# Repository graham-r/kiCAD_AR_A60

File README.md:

# A&R A60 Amplifier KICAD projects

NOTE: These are experiments in using KICAD - they are untested as they have not been built
(unless stated otherwise in the README file in a specific directory).

The projects contained in this repository are all based on the A&R A60 or A60AP integrated
amplifiers, currently limited to issue 8 (25502 onwards schematics).

The copyright of the circuits remain with the original owners, the Schematic and hardware
copyright are open source.

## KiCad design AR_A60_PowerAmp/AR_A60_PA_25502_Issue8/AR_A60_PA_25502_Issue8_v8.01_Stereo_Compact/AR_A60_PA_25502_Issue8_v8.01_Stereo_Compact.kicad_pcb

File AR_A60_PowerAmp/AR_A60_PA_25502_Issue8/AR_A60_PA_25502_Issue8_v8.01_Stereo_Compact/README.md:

# A&R A60 Amplifier KICAD projects

Version 8.01 differences

Compact style PCB Power & speaker fuses removed Common input socket (Left & Right) +/-36v Power rails decoupled between power amp stage & input stage

NOTE: These are experiments in using KICAD - they are untested as they have not been built (unless stated otherwise in the README file in a specific directory).

The projects contained in this repository are all based on the A&R A60 or A60AP integrated amplifiers, currently limited to issue 8 (25502 onwards schematics).

The copyright of the circuits remain with the original owners, the Schematic and hardware copyright are open source.

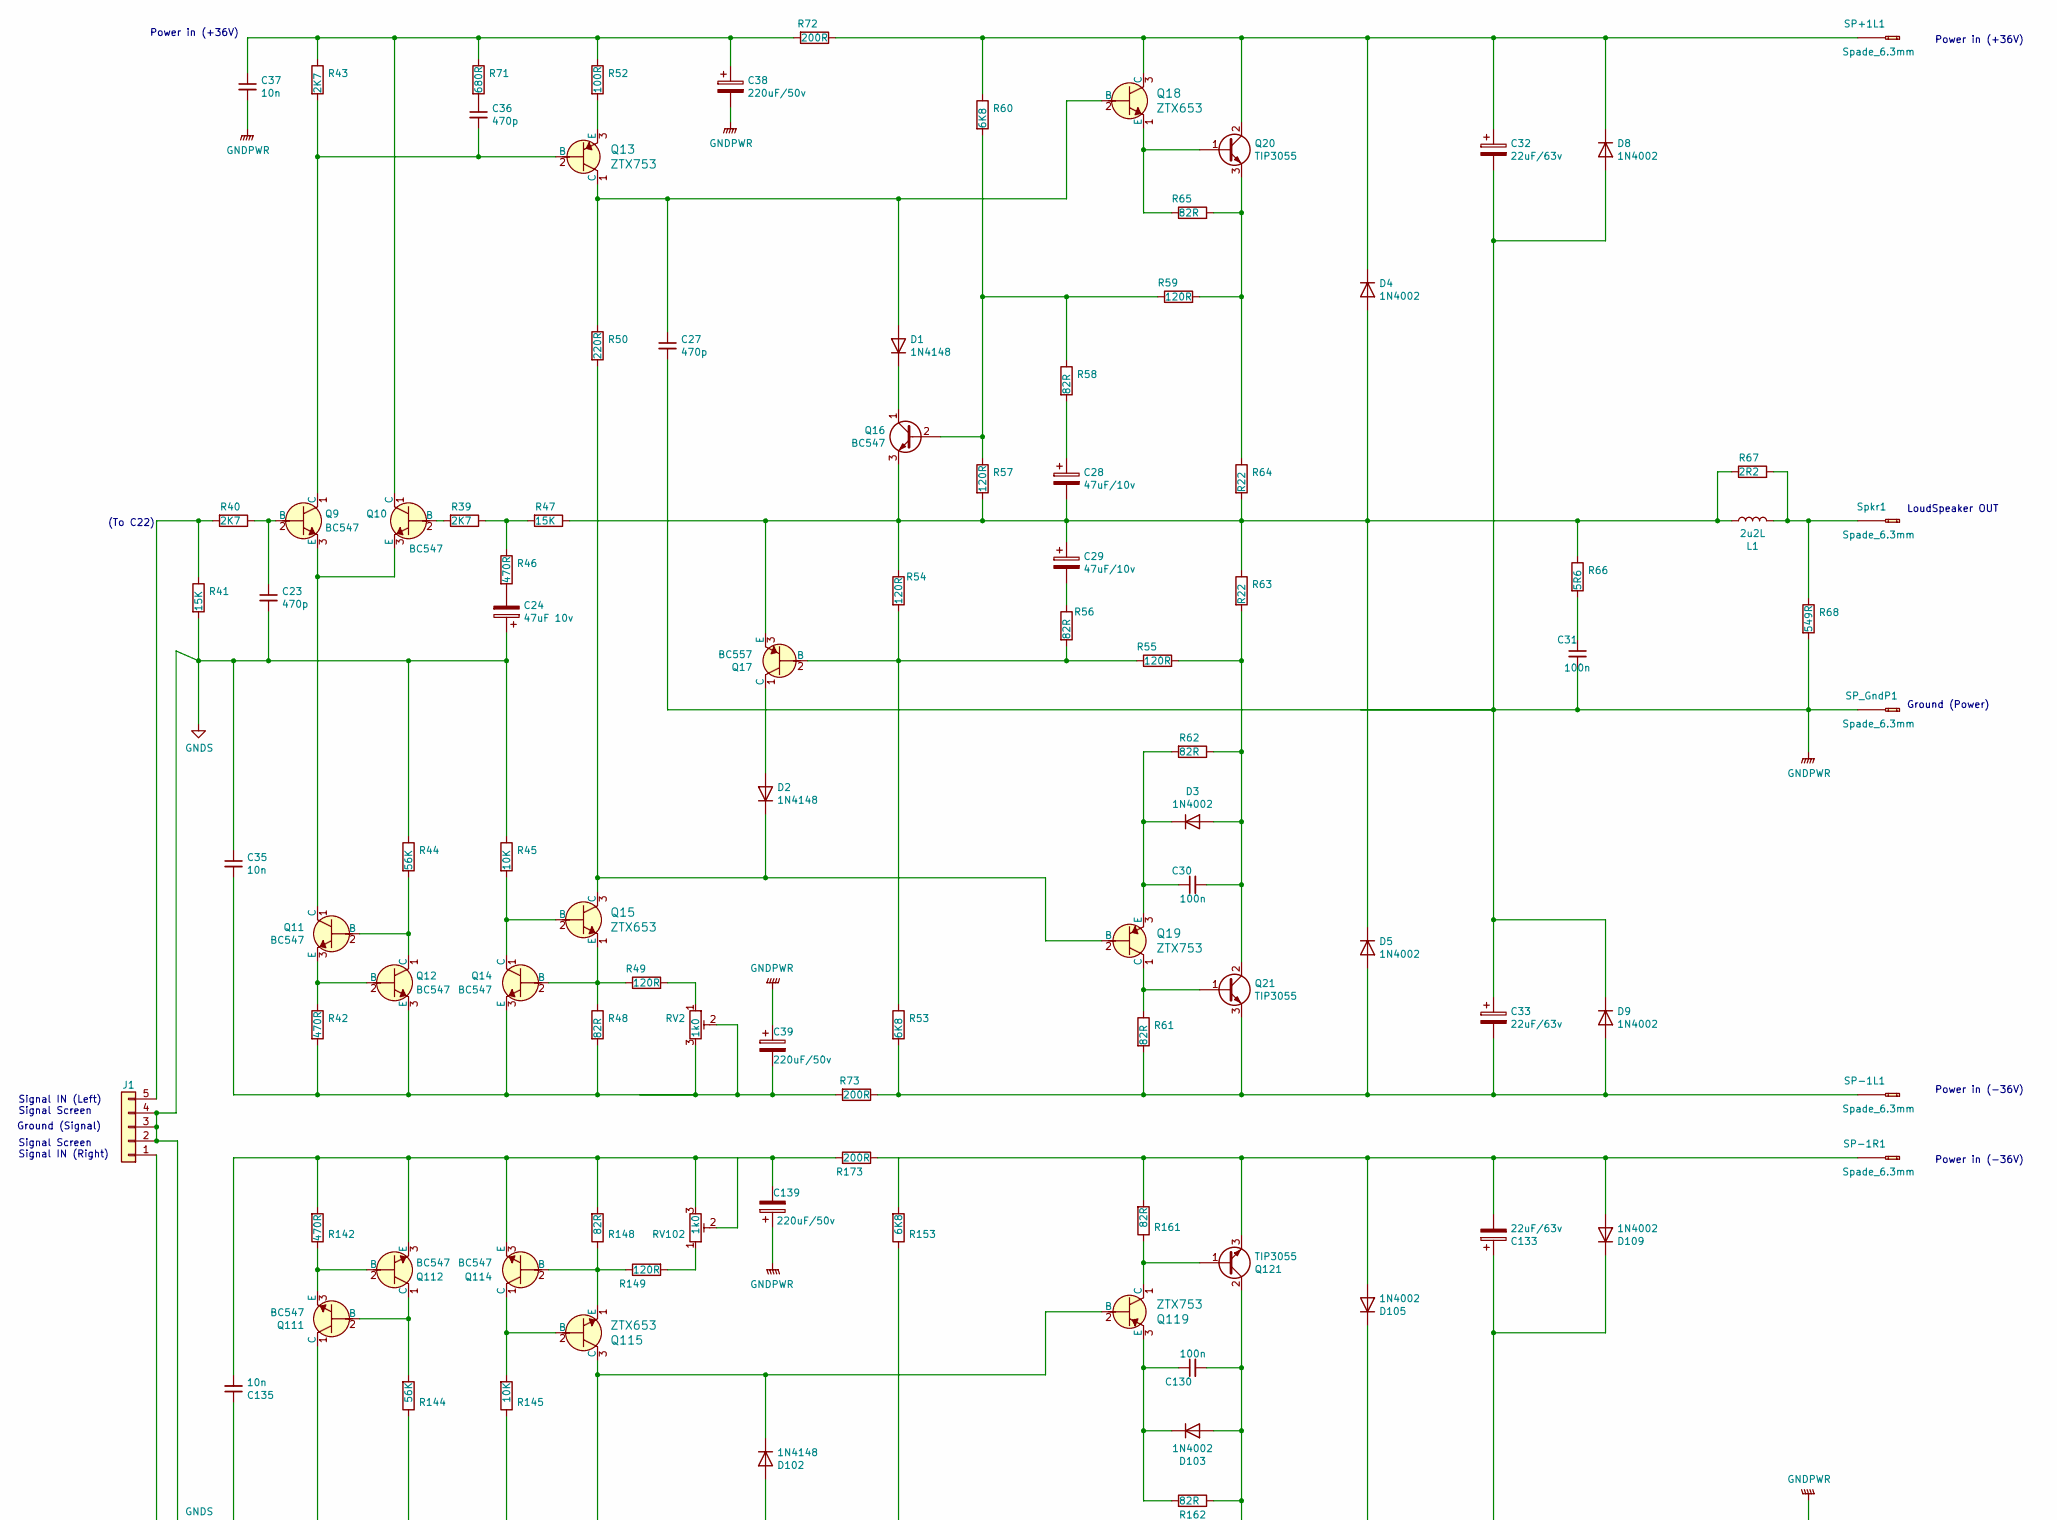
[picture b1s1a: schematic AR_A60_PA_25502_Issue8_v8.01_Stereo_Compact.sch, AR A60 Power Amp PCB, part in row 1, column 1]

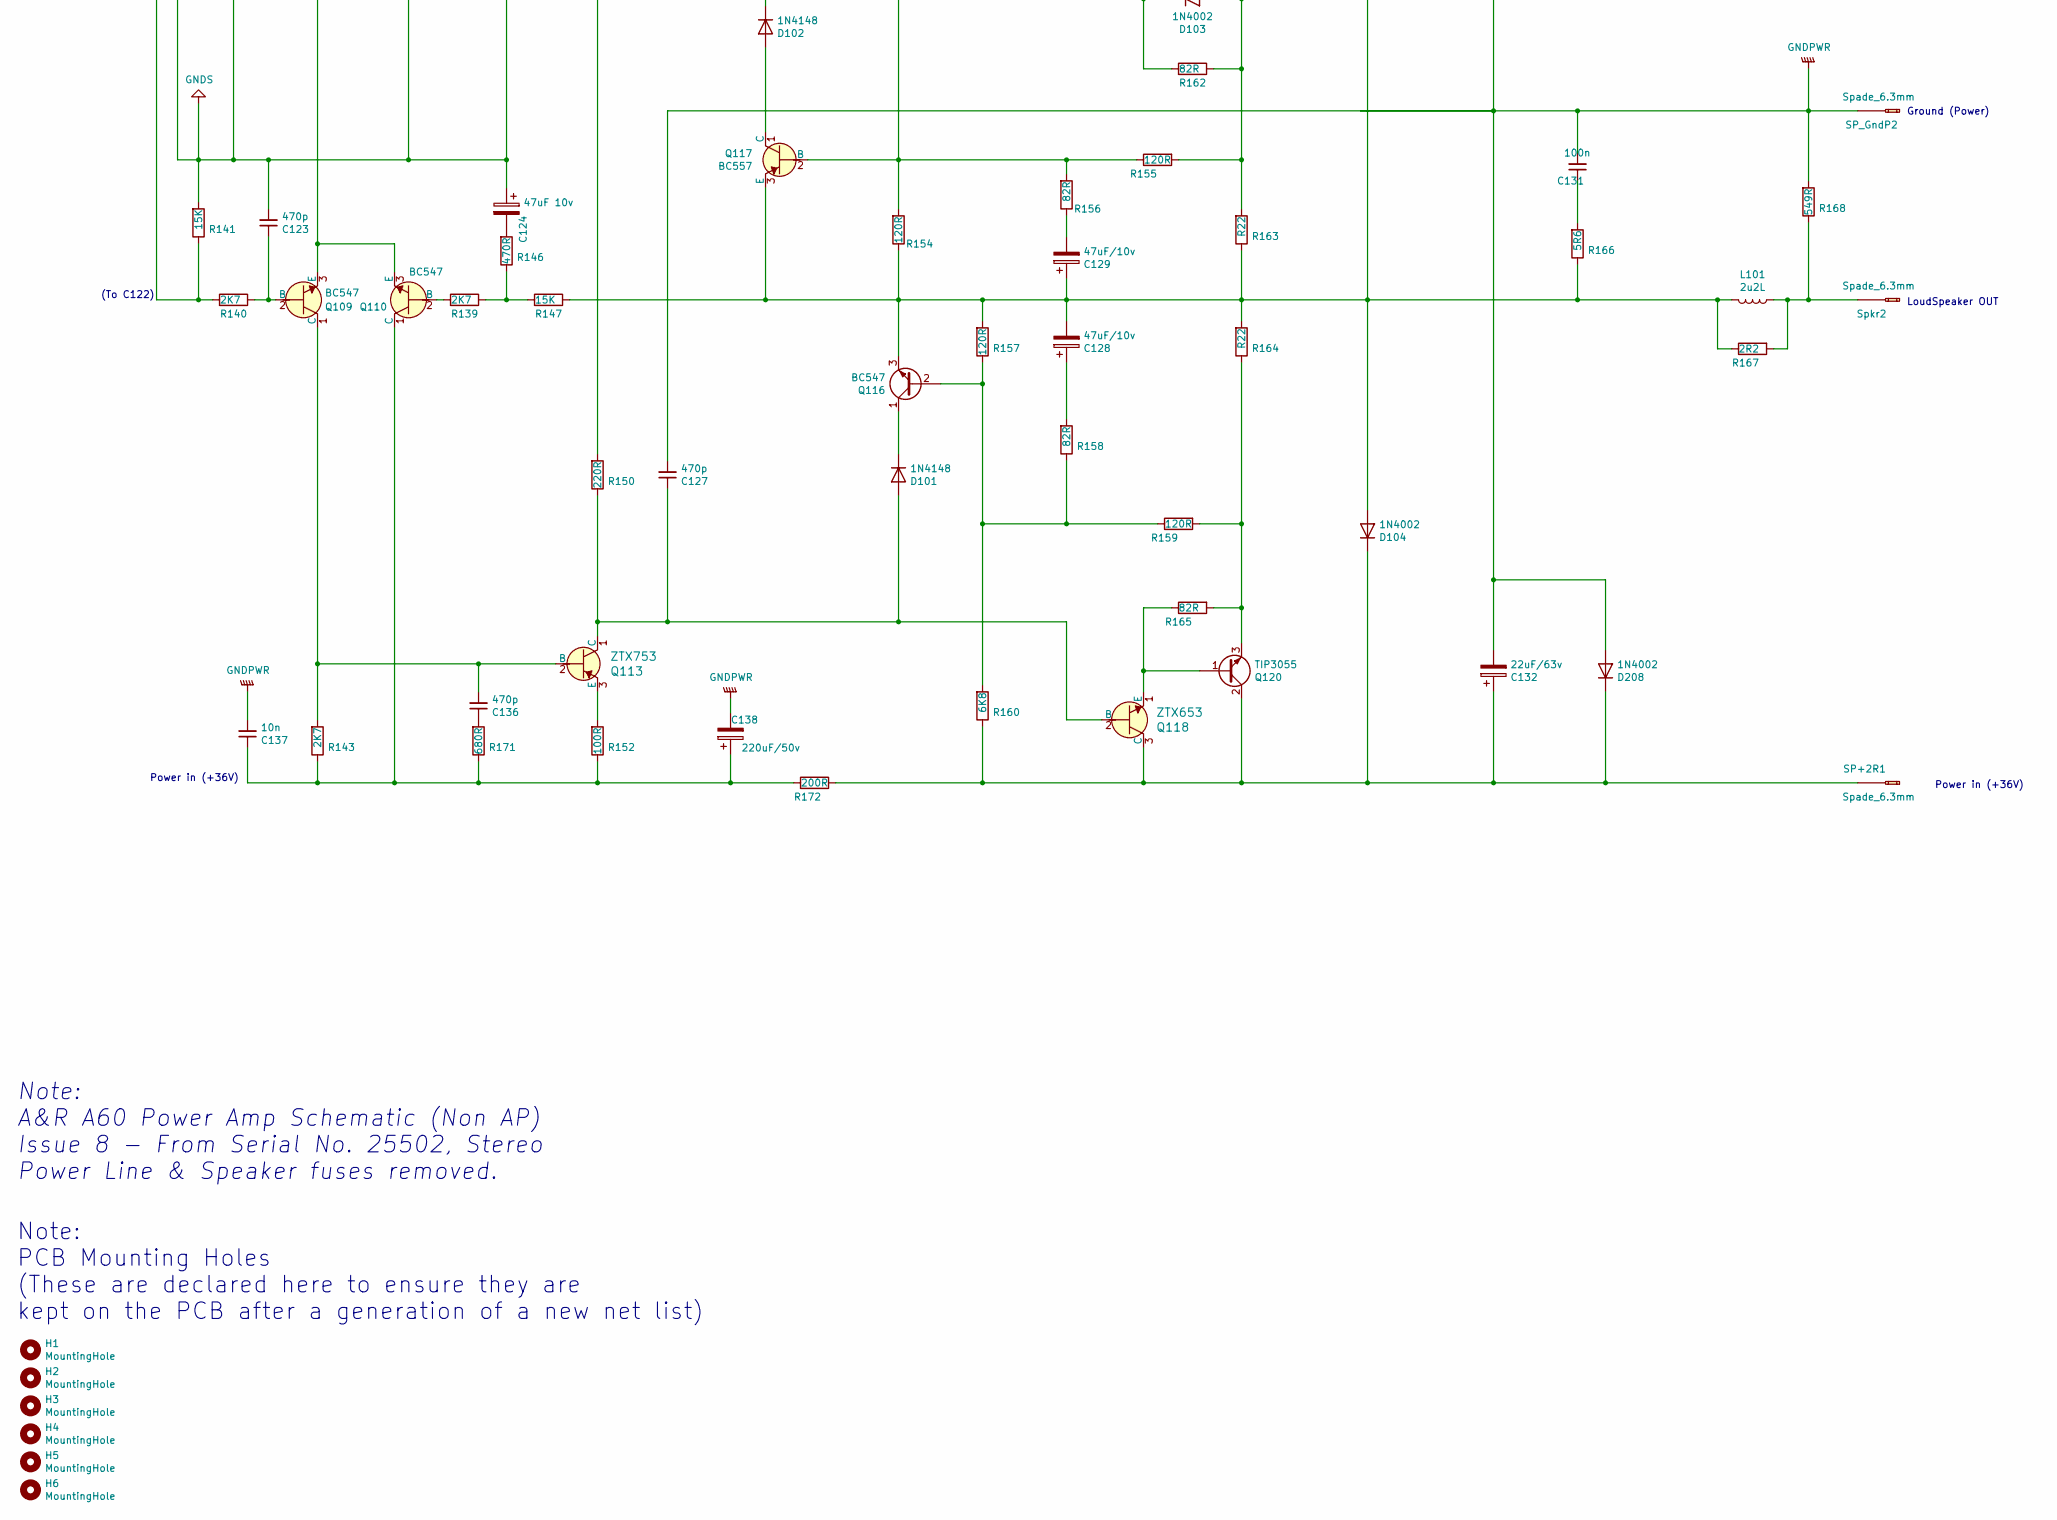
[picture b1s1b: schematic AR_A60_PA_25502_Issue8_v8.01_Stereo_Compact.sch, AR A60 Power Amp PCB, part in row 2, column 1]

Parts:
C23, C27, C36, C123, C127, C136: 470p; C_Rect_L7.0mm_W2.5mm_P5.00mm
C24, C124: 47uF 10v; CP_Radial_D8.0mm_P2.50mm
C28, C29, C128, C129: 47uF/10v; CP_Radial_D8.0mm_P2.50mm
C30, C31, C130, C131: 100n; C_Rect_L18.0mm_W7.0mm_P15.00mm_FKS3_FKP3
C32, C33, C132, C133: 22uF/63v; CP_Radial_D10.0mm_P5.00mm
C35, C37, C135, C137: 10n; C_Rect_L7.0mm_W2.5mm_P5.00mm
C38, C39, C138, C139: 220uF/50v; CP_Radial_D10.0mm_P5.00mm
D1, D2, D101, D102: 1N4148; D_DO-35_SOD27_P7.62mm_Horizontal
D3, D4, D5, D8, D9, D103, D104, D105, D109, D208: 1N4002; D_DO-41_SOD81_P10.16mm_Horizontal
H1, H2, H3, H4, H5, H6: MountingHole; MountingHole_3.5mm
J1: Conn_01x05; Molex_KK-254_AE-6410-05A_1x05_P2.54mm_Vertical
L1, L101: 2u2L; L_Axial_L16.0mm_D6.3mm_P20.32mm_Horizontal_Fastron_VHBCC
Q9, Q10, Q11, Q12, Q14, Q16, Q109, Q110, Q111, Q112, Q114, Q116: BC547; TO-92_Inline
Q13, Q19, Q113, Q119: ZTX753; TO-92-3; MPN ZTX753; Digi-Key_PN ZTX753-ND
Q15, Q18, Q115, Q118: ZTX653; TO-92-3; MPN ZTX653; Digi-Key_PN ZTX653-ND
Q17, Q117: BC557; TO-92_Inline
Q20, Q21, Q120, Q121: TIP3055; TO-218-3_Vertical
R39, R40, R43, R139, R140, R143: 2K7; R_Axial_DIN0309_L9.0mm_D3.2mm_P12.70mm_Horizontal
R41, R47, R141, R147: 15K; R_Axial_DIN0309_L9.0mm_D3.2mm_P12.70mm_Horizontal
R42, R46, R142, R146: 470R; R_Axial_DIN0309_L9.0mm_D3.2mm_P12.70mm_Horizontal
R44, R144: 56K; R_Axial_DIN0309_L9.0mm_D3.2mm_P12.70mm_Horizontal
R45, R145: 10K; R_Axial_DIN0309_L9.0mm_D3.2mm_P12.70mm_Horizontal
R48, R56, R58, R61, R62, R65, R148, R156, R158, R161, R162, R165: 82R; R_Axial_DIN0309_L9.0mm_D3.2mm_P12.70mm_Horizontal
R49, R54, R55, R57, R59, R149, R154, R155, R157, R159: 120R; R_Axial_DIN0309_L9.0mm_D3.2mm_P12.70mm_Horizontal
R50, R150: 220R; R_Axial_DIN0309_L9.0mm_D3.2mm_P12.70mm_Horizontal
R52, R152: 100R; R_Axial_DIN0309_L9.0mm_D3.2mm_P12.70mm_Horizontal
R53, R60, R153, R160: 6K8; R_Axial_DIN0309_L9.0mm_D3.2mm_P12.70mm_Horizontal
R63, R64, R163, R164: R22; R_Axial_DIN0516_L15.5mm_D5.0mm_P25.40mm_Horizontal
R66, R166: 5R6; R_Axial_DIN0309_L9.0mm_D3.2mm_P12.70mm_Horizontal
R67, R167: 2R2; R_Axial_DIN0309_L9.0mm_D3.2mm_P12.70mm_Horizontal
R68, R168: 549R; R_Axial_DIN0309_L9.0mm_D3.2mm_P12.70mm_Horizontal
R71, R171: 680R; R_Axial_DIN0309_L9.0mm_D3.2mm_P12.70mm_Horizontal
R72, R73, R172, R173: 200R; R_Axial_DIN0309_L9.0mm_D3.2mm_P12.70mm_Horizontal
RV2, RV102: 1k0; Potentiometer_Bourns_3296W_Vertical
SP+1L1, SP+2R1: Spade_6.3mm; SPADE_TERMINAL_6.3MM
SP-1L1, SP-1R1: Spade_6.3mm; SPADE_TERMINAL_6.3MM
SP_GndP1, SP_GndP2: Spade_6.3mm; SPADE_TERMINAL_6.3MM
Spkr1, Spkr2: Spade_6.3mm; SPADE_TERMINAL_6.3MM

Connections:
GNDPWR: C27.2, C31.2, C32.2, C33.1, C37.2, C38.2, C39.1, C127.2, C131.2, C132.2, C133.1, C137.2, C138.2, C139.1, D8.2 (A), D9.1 (K), D109.1 (K), D208.2 (A), R68.2, R168.2, SP_GndP1.1, SP_GndP2.1
GNDS: C23.2, C24.1, C35.1, C123.2, C124.1, C135.1, J1.2, J1.3, J1.4, R41.2, R44.1, R45.1, R141.2, R144.1, R145.1
unnamed: C23.1, Q9.2 (B), R40.1
unnamed: C24.2, R46.2
unnamed: C27.1, D1.2 (A), Q13.1 (C), Q18.2 (B), R50.1
unnamed: C28.1, R58.2
unnamed: C28.2, C29.1, D4.2 (A), D5.1 (K), L1.1, Q16.3 (E), Q17.3 (E), R47.1, R54.1, R57.2, R63.1, R64.2, R66.1, R67.1
unnamed: C29.2, R56.1
unnamed: C30.1, D3.1 (K), Q19.3 (E), R62.2
unnamed: C30.2, D3.2 (A), Q21.2 (C), R55.2, R62.1, R63.2
unnamed: C31.1, R66.2
unnamed: C32.1, D4.1 (K), D8.1 (K), Q18.3 (C), Q20.2 (C), R60.1, R72.1, SP+1L1.1
unnamed: C33.2, D5.2 (A), D9.2 (A), Q21.3 (E), R53.2, R61.2, R73.1, SP-1L1.1
unnamed: C35.2, C39.2, Q12.3 (E), Q14.3 (E), R42.2, R48.2, R73.2, RV2.2, RV2.3
unnamed: C36.1, R71.2
unnamed: C36.2, Q9.1 (C), Q13.2 (B), R43.2
unnamed: C37.1, C38.1, Q10.1 (C), R43.1, R52.1, R71.1, R72.2
unnamed: C123.1, Q109.2 (B), R140.1
unnamed: C124.2, R146.2
unnamed: C127.1, D101.2 (A), Q113.1 (C), Q118.2 (B), R150.1
unnamed: C128.1, R158.2
unnamed: C128.2, C129.1, D104.2 (A), D105.1 (K), L101.1, Q116.3 (E), Q117.3 (E), R147.1, R154.1, R157.2, R163.1, R164.2, R166.1, R167.1
unnamed: C129.2, R156.1
unnamed: C130.1, D103.1 (K), Q119.3 (E), R162.2
unnamed: C130.2, D103.2 (A), Q121.2 (C), R155.2, R162.1, R163.2
unnamed: C131.1, R166.2
unnamed: C132.1, D104.1 (K), D208.1 (K), Q118.3 (C), Q120.2 (C), R160.1, R172.1, SP+2R1.1
unnamed: C133.2, D105.2 (A), D109.2 (A), Q121.3 (E), R153.2, R161.2, R173.1, SP-1R1.1
unnamed: C135.2, C139.2, Q112.3 (E), Q114.3 (E), R142.2, R148.2, R173.2, RV102.2, RV102.3
unnamed: C136.1, R171.2
unnamed: C136.2, Q109.1 (C), Q113.2 (B), R143.2
unnamed: C137.1, C138.1, Q110.1 (C), R143.1, R152.1, R171.1, R172.2
unnamed: D1.1 (K), Q16.1 (C)
unnamed: D2.1 (K), Q15.3 (C), Q19.2 (B), R50.2
unnamed: D2.2 (A), Q17.1 (C)
unnamed: D101.1 (K), Q116.1 (C)
unnamed: D102.1 (K), Q115.3 (C), Q119.2 (B), R150.2
unnamed: D102.2 (A), Q117.1 (C)
unnamed: J1.1, R140.2, R141.1
unnamed: J1.5, R40.2, R41.1
unnamed: L1.2, R67.2, R68.1, Spkr1.1
unnamed: L101.2, R167.2, R168.1, Spkr2.1
unnamed: Q10.2 (B), R39.2
unnamed: Q9.3 (E), Q10.3 (E), Q11.1 (C)
unnamed: Q11.2 (B), Q12.1 (C), R44.2
unnamed: Q11.3 (E), Q12.2 (B), R42.1
unnamed: Q13.3 (E), R52.2
unnamed: Q14.1 (C), Q15.2 (B), R45.2
unnamed: Q14.2 (B), Q15.1 (E), R48.1, R49.1
unnamed: Q16.2 (B), R57.1, R58.1, R59.1, R60.2
unnamed: Q17.2 (B), R53.1, R54.2, R55.1, R56.2
unnamed: Q18.1 (E), Q20.1 (B), R65.1
unnamed: Q19.1 (C), Q21.1 (B), R61.1
unnamed: Q20.3 (E), R59.2, R64.1, R65.2
unnamed: Q109.3 (E), Q110.3 (E), Q111.1 (C)
unnamed: Q110.2 (B), R139.2
unnamed: Q111.2 (B), Q112.1 (C), R144.2
unnamed: Q111.3 (E), Q112.2 (B), R142.1
unnamed: Q113.3 (E), R152.2
unnamed: Q114.1 (C), Q115.2 (B), R145.2
unnamed: Q114.2 (B), Q115.1 (E), R148.1, R149.1
unnamed: Q116.2 (B), R157.1, R158.1, R159.1, R160.2
unnamed: Q117.2 (B), R153.1, R154.2, R155.1, R156.2
unnamed: Q118.1 (E), Q120.1 (B), R165.1
unnamed: Q119.1 (C), Q121.1 (B), R161.1
unnamed: Q120.3 (E), R159.2, R164.1, R165.2
unnamed: R39.1, R46.1, R47.2
unnamed: R49.2, RV2.1
unnamed: R139.1, R146.1, R147.2
unnamed: R149.2, RV102.1

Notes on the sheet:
(To C22)
Power in (-36V)
Power in (+36V)
Note: A&R A60 Power Amp Schematic (Non AP) Issue 8 - From Serial No. 25502, Stereo Power Line & Speaker fuses removed.
Note: PCB Mounting Holes (These are declared here to ensure they are kept on the PCB after a generation of a new net list)
LoudSpeaker OUT
Ground (Power)
(To C122)
Signal Screen Signal IN (Right)
Ground (Signal)
Signal IN (Left) Signal Screen

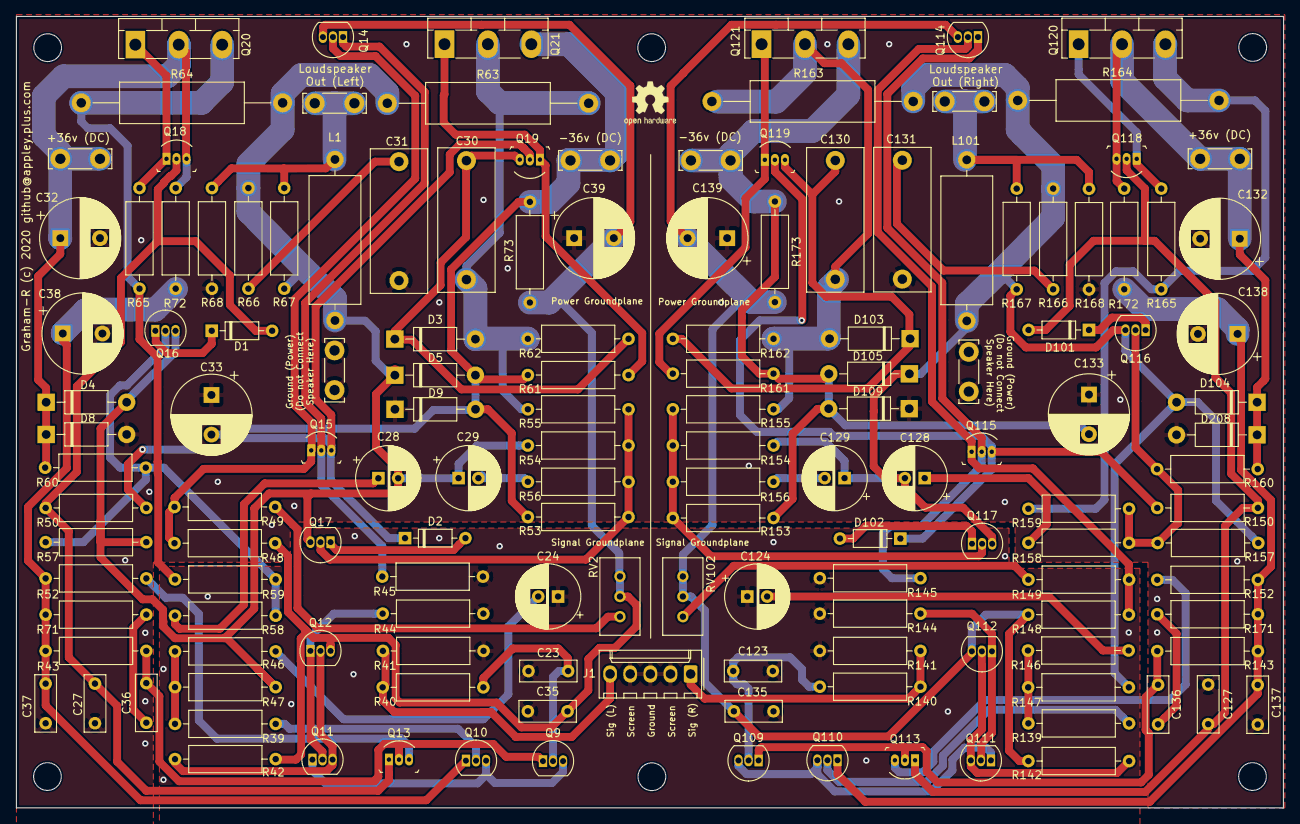
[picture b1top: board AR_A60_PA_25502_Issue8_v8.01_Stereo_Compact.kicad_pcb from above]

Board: 2 copper layers, 159.9 x 99.9 mm, 151 parts (0 on the bottom side), 70 nets.

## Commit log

2020-04-24 Initial commit for version 8.0 Power Amps
2020-04-25 Updated .gitignore files
2020-04-25 Remove Archive directory
2020-04-25 Added README.md file
2020-04-25 Updated polycarb caps
2020-04-28 Added new Stereo compact (for future car amp) A60 Amplifier PCB
2020-04-28 Update 1

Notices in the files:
AR_A60_PowerAmp/AR_A60_PA_25502_Issue8/AR_A60_PA_25502_Issue8_v8.01_Stereo_Compact/AR_A60_PA_25502_Issue8_v8.01_Stereo_Compact.kicad_pcb:
Graham-R (c) 2020 github@appley.plus.com
